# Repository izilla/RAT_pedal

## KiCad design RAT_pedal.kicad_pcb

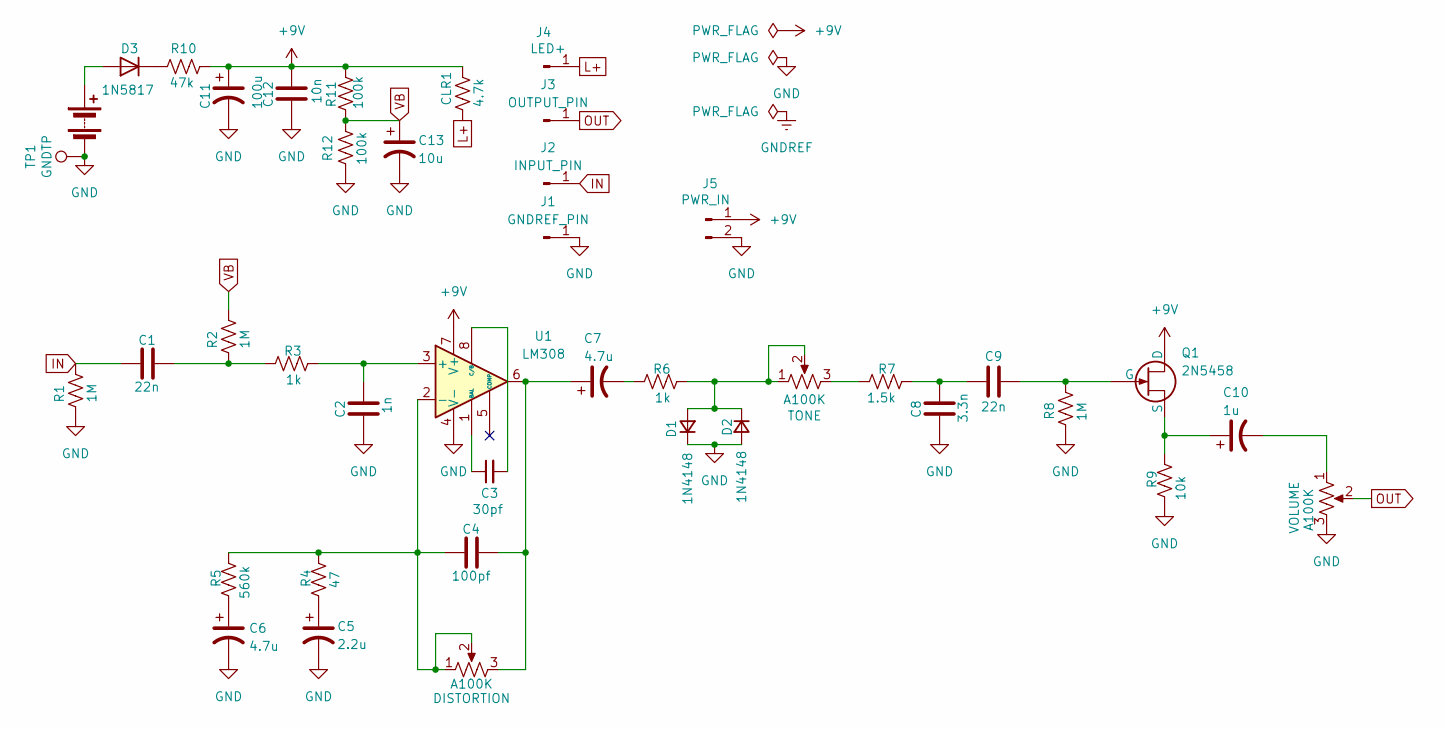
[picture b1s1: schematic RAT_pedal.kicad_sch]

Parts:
BT1: Battery; Molex_KK-254_AE-6410-02A_1x02_P2.54mm_Vertical
C1, C9: 22n; C_Disc_D4.3mm_W1.9mm_P5.00mm
C2: 1n; C_Disc_D4.3mm_W1.9mm_P5.00mm
C3: 30pf; C_Disc_D4.3mm_W1.9mm_P5.00mm
C4: 100pf; C_Disc_D4.3mm_W1.9mm_P5.00mm
C5: 2.2u; CP_Radial_D5.0mm_P2.00mm
C6, C7: 4.7u; CP_Radial_D5.0mm_P2.00mm
C8: 3.3n; C_Disc_D4.3mm_W1.9mm_P5.00mm
C10: 1u; CP_Radial_D5.0mm_P2.00mm
C11: 100u; CP_Radial_D5.0mm_P2.00mm
C12: 10n; C_Disc_D4.3mm_W1.9mm_P5.00mm
C13: 10u; CP_Radial_D5.0mm_P2.00mm
CLR1: 4.7k; R_Axial_DIN0204_L3.6mm_D1.6mm_P5.08mm_Horizontal
D1, D2: 1N4148; D_DO-35_SOD27_P7.62mm_Horizontal
D3: 1N5817; D_DO-41_SOD81_P7.62mm_Horizontal
J1: GNDREF_PIN; TestPoint_THTPad_D1.0mm_Drill0.5mm
J2: INPUT_PIN; PinHeader_1x01_P1.00mm_Vertical
J3: OUTPUT_PIN; PinHeader_1x01_P1.00mm_Vertical
J4: LED+; PinHeader_1x01_P1.00mm_Vertical
J5: POWER_IN; PinHeader_1x02_P2.54mm_Vertical
POT1, POT2, POT3: A100K; PinHeader_1x03_P2.00mm_Vertical
Q1: 2N5458; TO-92_Inline
R1, R2, R8: 1M; R_Axial_DIN0309_L9.0mm_D3.2mm_P12.70mm_Horizontal
R3, R6: 1k; R_Axial_DIN0309_L9.0mm_D3.2mm_P12.70mm_Horizontal
R4: 47; R_Axial_DIN0207_L6.3mm_D2.5mm_P7.62mm_Horizontal
R5: 560k; R_Axial_DIN0309_L9.0mm_D3.2mm_P12.70mm_Horizontal
R7: 1.5k; R_Axial_DIN0309_L9.0mm_D3.2mm_P12.70mm_Horizontal
R9: 10k; R_Axial_DIN0309_L9.0mm_D3.2mm_P12.70mm_Horizontal
R10: 47k; R_Axial_DIN0204_L3.6mm_D1.6mm_P5.08mm_Horizontal
R11, R12: 100k; R_Axial_DIN0204_L3.6mm_D1.6mm_P5.08mm_Horizontal
TP1: GNDTP; TestPoint_Pad_D2.5mm
U1: LM308; DIP-8_W7.62mm_Socket

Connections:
+9V: C11.1, C12.1, CLR1.2, J5.1, Q1.1 (D), R10.2, R11.2, U1.7 (V+)
GND: BT1.2 (-), C2.1, C5.2, C6.2, C8.1, C11.2, C12.2, C13.2, D1.1 (K), D2.2 (A), J1.1, J5.2, POT3.3, R1.1, R8.2, R9.2, R12.1, TP1.1, U1.4 (V-)
IN: C1.1, J2.1, R1.2
L+: CLR1.1, J4.1
unnamed: BT1.1 (+), D3.2 (A)
unnamed: C1.2, R2.1, R3.2
unnamed: C4.2, C7.1, POT1.3, U1.6
unnamed: C5.1, R4.2
unnamed: C6.1, R5.2
unnamed: C7.2, R6.2
unnamed: C8.2, C9.1, R7.1
unnamed: C10.2, POT3.1
unnamed: D1.2 (A), D2.1 (K), POT2.1, POT2.2, R6.1
unnamed: D3.1 (K), R10.1
unnamed: POT2.3, R7.2
unnamed: C9.2, Q1.2 (G), R8.1
unnamed: C10.1, Q1.3 (S), R9.1
unnamed: C2.2, R3.1, U1.3 (+)
unnamed: C4.1, POT1.1, POT1.2, R4.1, R5.1, U1.2 (-)
unnamed: C3.1, U1.1 (BAL)
unnamed: C3.2, U1.8 (C/B)
OUT: J3.1, POT3.2
VB: C13.1, R2.2, R11.1, R12.2

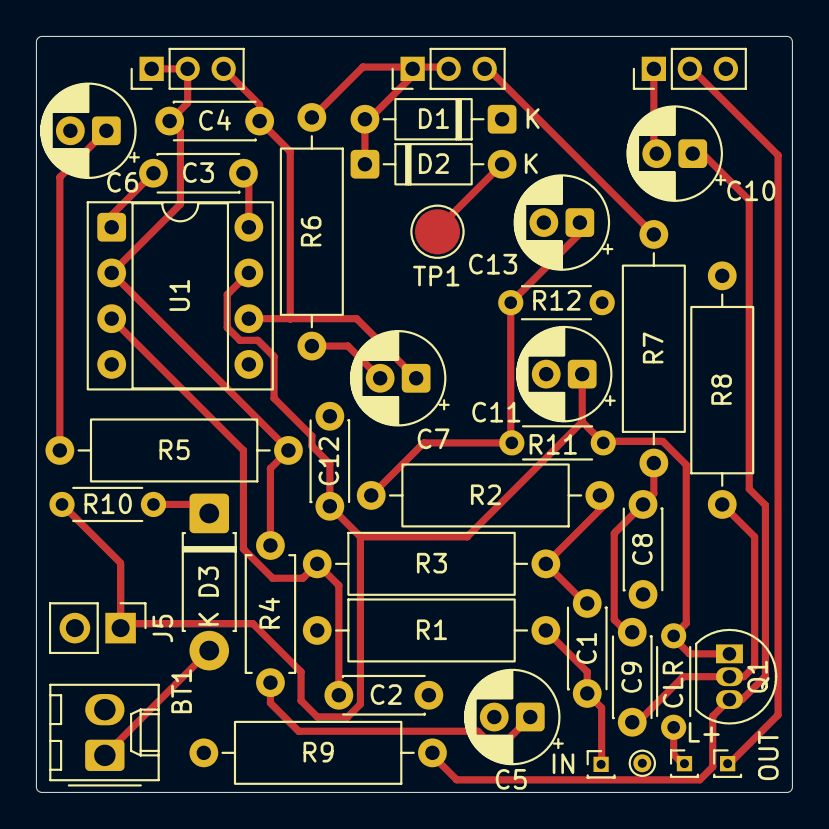
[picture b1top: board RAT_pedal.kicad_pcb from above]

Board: 2 copper layers, 42.0 x 42.0 mm, 41 parts (0 on the bottom side), 23 nets.

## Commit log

2025-10-11 init
2025-10-13 ignore fp-info cache
2025-11-02 Updates yo
